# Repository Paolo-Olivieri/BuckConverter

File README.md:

# BuckConverter
Progetto del corso Progettazione dei Sistemi Elettronici - UNIBG

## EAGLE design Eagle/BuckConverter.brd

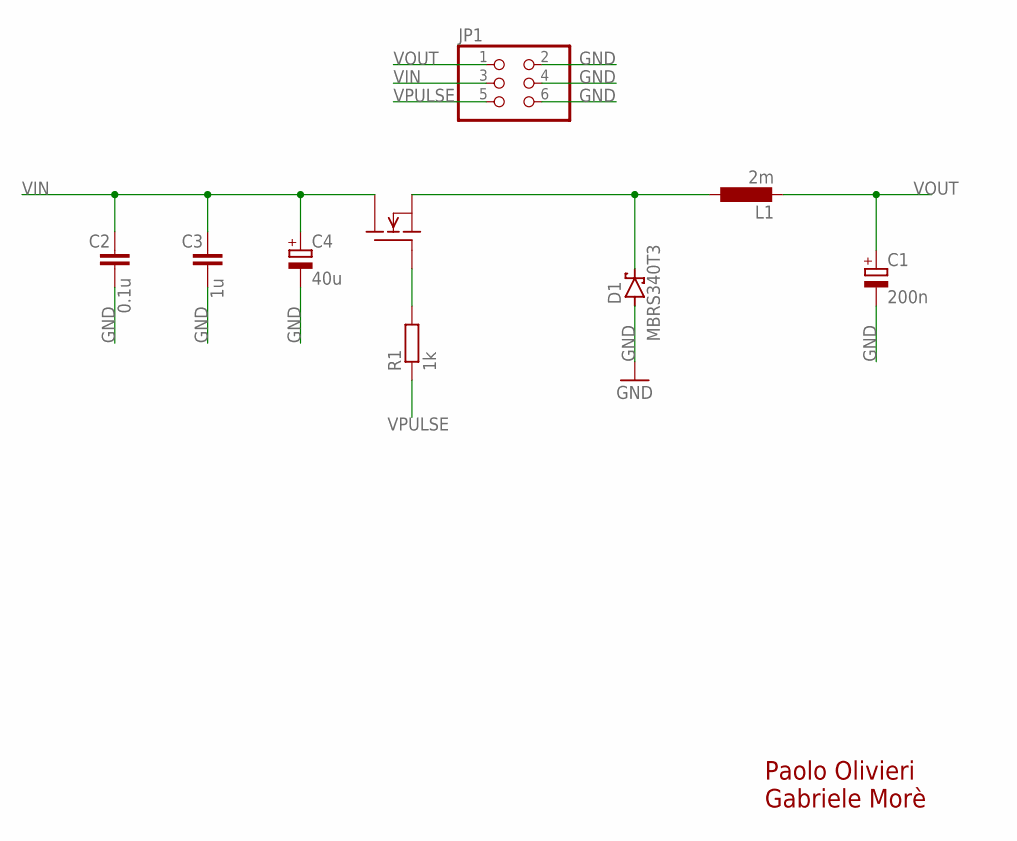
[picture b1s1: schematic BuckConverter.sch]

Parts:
C1: 200n; B/3528-21W
C2: 0.1u; C0805
C3: 1u; C0805
C4: 40u; B/3528-21W
D1: MBRS340T3; SMC
JP1: PINHD-2X3; 2X03
L1: 2m; L1812
Q1: IRF540; TO220
R1: 1k; R0805

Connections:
GND: C1.-, C2.2, C3.2, C4.-, D1.A, JP1.2, JP1.4, JP1.6
unnamed: D1.C, L1.1, Q1.3 (S)
unnamed: Q1.1 (G), R1.2
VIN: C2.1, C3.1, C4.+, JP1.3, Q1.2 (D)
VOUT: C1.+, JP1.1, L1.2
VPULSE: JP1.5, R1.1

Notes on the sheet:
Paolo Olivieri Gabriele Morè

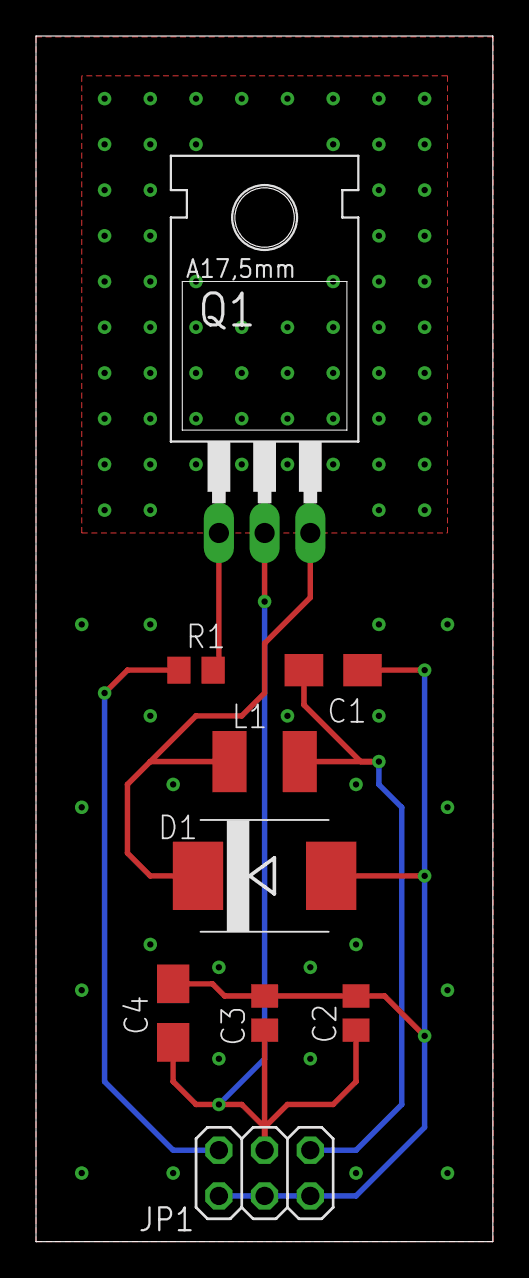
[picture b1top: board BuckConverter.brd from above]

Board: 2 copper layers, 25.4 x 67.0 mm, 9 parts (0 on the bottom side), 6 nets.
